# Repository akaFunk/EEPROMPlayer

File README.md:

# EEPROMPlayer
The EEPROMPlayer is an audio player that can play audio from an (E)EPROM using no microcontroller, but only simple logic ICs and an analog audio amplifier.

The EPROM used is compatible to standard 27C010 EPROMs. The clock is generated using an NE555 timer and then diveded several times using 74LS74 flip-flops. Each clock signal is fed to one of the address lines of the EPROM. The EPROM holds the raw audio data in 8 bit. The 8 data lines are passed into an R2R-network which does the digital to analog conversion. An LM386 is used to amplify the signal.

## Images

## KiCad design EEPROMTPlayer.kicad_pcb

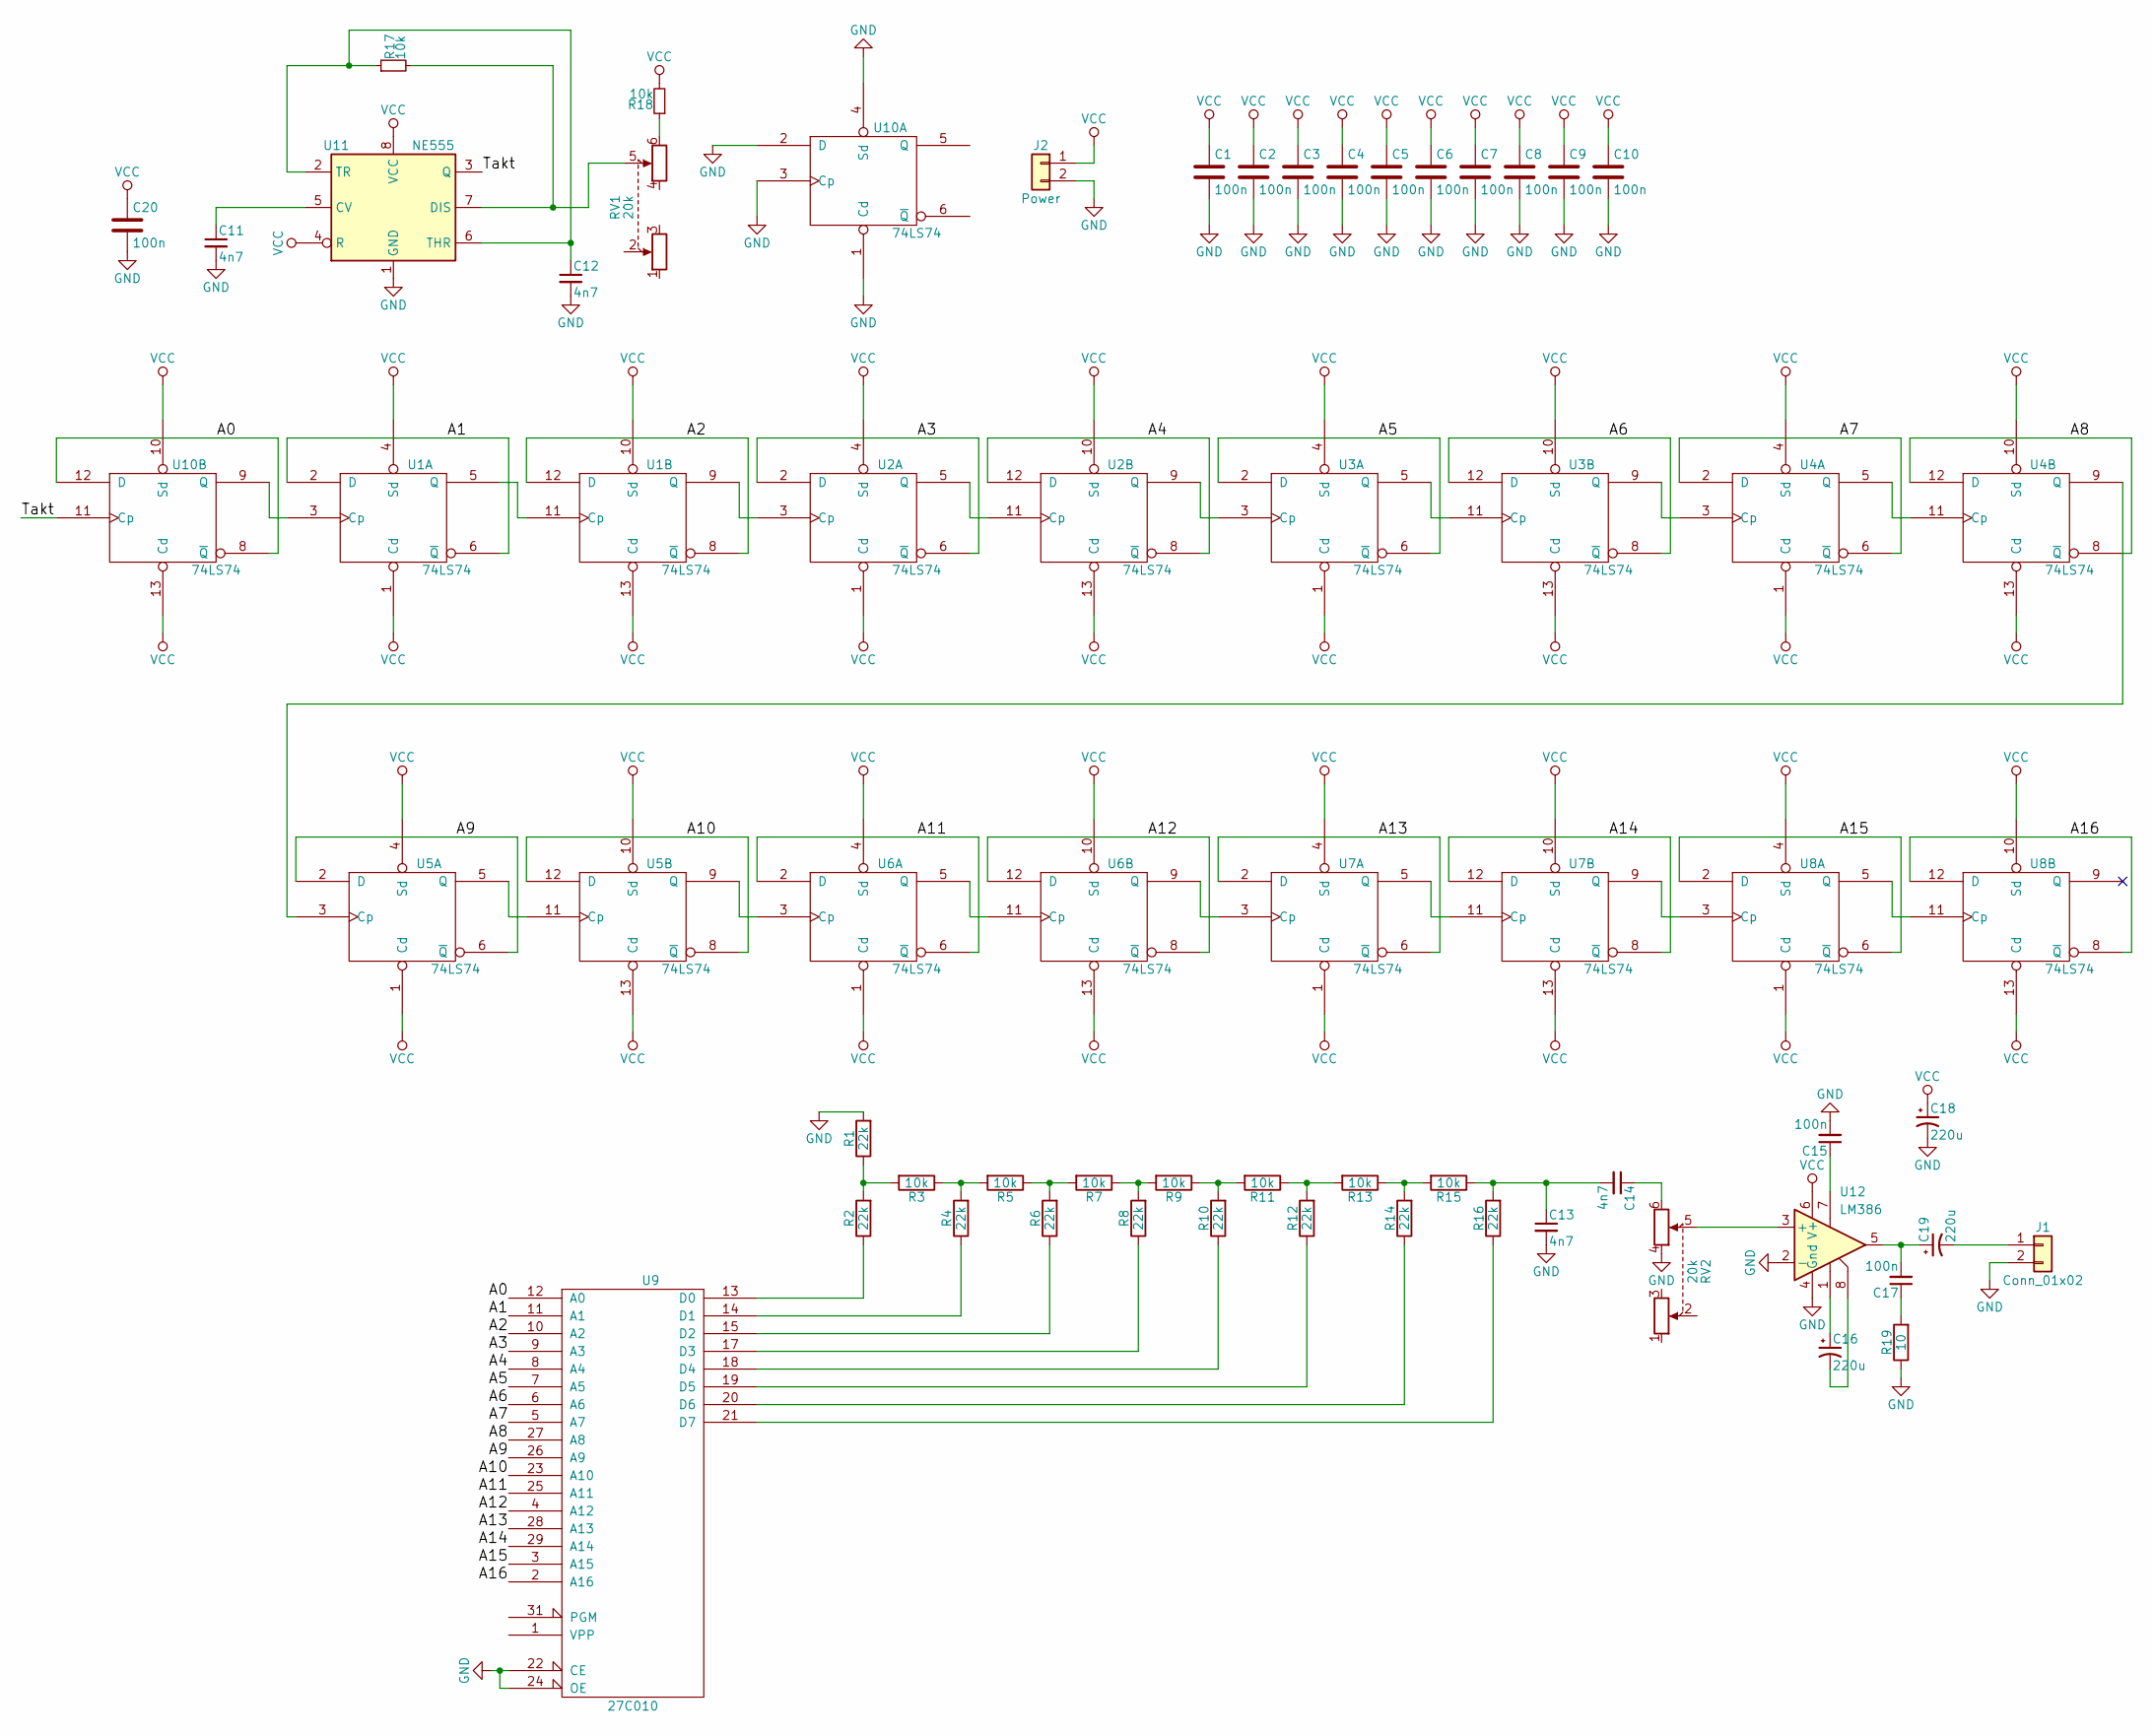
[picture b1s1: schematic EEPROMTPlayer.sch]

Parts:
C1, C2, C3, C4, C5, C6, C7, C8, C9, C10, C15, C17, C20: 100n; C_Disc_D3.0mm_W1.6mm_P2.50mm
C11, C12, C13, C14: 4n7; C_Disc_D12.5mm_W5.0mm_P10.00mm
C16, C18, C19: 220u; CP_Radial_D6.3mm_P2.50mm
J1: Conn_01x02; Pin_Header_Straight_1x02_Pitch2.54mm
J2: Power; Pin_Header_Straight_1x02_Pitch2.54mm
R1, R2, R4, R6, R8, R10, R12, R14, R16: 22k; R_Axial_DIN0204_L3.6mm_D1.6mm_P7.62mm_Horizontal
R3, R5, R7, R9, R11, R13, R15: 10k; R_Axial_DIN0204_L3.6mm_D1.6mm_P2.54mm_Vertical
R17, R18: 10k; R_Axial_DIN0204_L3.6mm_D1.6mm_P7.62mm_Horizontal
R19: 10; R_Axial_DIN0204_L3.6mm_D1.6mm_P7.62mm_Horizontal
RV1, RV2: 20k; Potentiometer_Alps_RK163_Double_Vertical
U1, U2, U3, U4, U5, U6, U7, U8, U10: 74LS74; DIP-14_W7.62mm_LongPads
U9: 27C010; DIP-32_W15.24mm_LongPads
U11: NE555; DIP-8_W7.62mm_LongPads
U12: LM386; DIP-8_W7.62mm_LongPads

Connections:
/A0: U9.12 (A0), U10.8 (~Q), U10.12 (D)
/A1: U1.2 (D), U1.6 (~Q), U9.11 (A1)
/A2: U1.8 (~Q), U1.12 (D), U9.10 (A2)
/A3: U2.2 (D), U2.6 (~Q), U9.9 (A3)
/A4: U2.8 (~Q), U2.12 (D), U9.8 (A4)
/A5: U3.2 (D), U3.6 (~Q), U9.7 (A5)
/A6: U3.8 (~Q), U3.12 (D), U9.6 (A6)
/A7: U4.2 (D), U4.6 (~Q), U9.5 (A7)
/A8: U4.8 (~Q), U4.12 (D), U9.27 (A8)
/A9: U5.2 (D), U5.6 (~Q), U9.26 (A9)
/A10: U5.8 (~Q), U5.12 (D), U9.23 (A10)
/A11: U6.2 (D), U6.6 (~Q), U9.25 (A11)
/A12: U6.8 (~Q), U6.12 (D), U9.4 (A12)
/A13: U7.2 (D), U7.6 (~Q), U9.28 (A13)
/A14: U7.8 (~Q), U7.12 (D), U9.29 (A14)
/A15: U8.2 (D), U8.6 (~Q), U9.3 (A15)
/A16: U8.8 (~Q), U8.12 (D), U9.2 (A16)
/Takt: U10.11 (Cp), U11.3 (Q)
GND: C1.2, C2.2, C3.2, C4.2, C5.2, C6.2, C7.2, C8.2, C9.2, C10.2, C11.2, C12.2, C13.2, C15.2, C18.2, C20.2, J1.2, J2.2, R1.2, R19.1, RV2.4, U1.7 (GND), U2.7 (GND), U3.7 (GND), U4.7 (GND), U5.7 (GND), U6.7 (GND), U7.7 (GND), U8.7 (GND), U9.16 (GND), U9.22 (CE), U9.24 (OE), U10.1 (Cd), U10.2 (D), U10.3 (Cp), U10.4 (Sd), U10.7 (GND), U11.1 (GND), U12.2 (-), U12.4 (Gnd)
unnamed: C11.1, U11.5 (CV)
unnamed: C12.1, R17.1, U11.2 (TR), U11.6 (THR)
unnamed: C13.1, C14.2, R15.1, R16.2
unnamed: C14.1, RV2.6
unnamed: C15.1, U12.7
unnamed: C16.1, U12.1
unnamed: C16.2, U12.8
unnamed: C17.1, R19.2
unnamed: C17.2, C19.1, U12.5
unnamed: C19.2, J1.1
unnamed: R1.1, R2.2, R3.2
unnamed: R2.1, U9.13 (D0)
unnamed: R3.1, R4.2, R5.2
unnamed: R4.1, U9.14 (D1)
unnamed: R5.1, R6.2, R7.2
unnamed: R6.1, U9.15 (D2)
unnamed: R7.1, R8.2, R9.2
unnamed: R8.1, U9.17 (D3)
unnamed: R10.1, U9.18 (D4)
unnamed: R9.1, R10.2, R11.2
unnamed: R11.1, R12.2, R13.2
unnamed: R12.1, U9.19 (D5)
unnamed: R13.1, R14.2, R15.2
unnamed: R14.1, U9.20 (D6)
unnamed: R16.1, U9.21 (D7)
unnamed: R17.2, RV1.5, U11.7 (DIS)
unnamed: R18.1, RV1.6
unnamed: RV2.5, U12.3 (+)
unnamed: U1.3 (Cp), U10.9 (Q)
unnamed: U1.9 (Q), U2.3 (Cp)
unnamed: U1.5 (Q), U1.11 (Cp)
unnamed: U2.9 (Q), U3.3 (Cp)
unnamed: U2.5 (Q), U2.11 (Cp)
unnamed: U3.9 (Q), U4.3 (Cp)
unnamed: U3.5 (Q), U3.11 (Cp)
unnamed: U4.9 (Q), U5.3 (Cp)
unnamed: U4.5 (Q), U4.11 (Cp)
unnamed: U5.9 (Q), U6.3 (Cp)
unnamed: U5.5 (Q), U5.11 (Cp)
unnamed: U6.9 (Q), U7.3 (Cp)
unnamed: U6.5 (Q), U6.11 (Cp)
unnamed: U7.9 (Q), U8.3 (Cp)
unnamed: U7.5 (Q), U7.11 (Cp)
unnamed: U8.5 (Q), U8.11 (Cp)
VCC: C1.1, C2.1, C3.1, C4.1, C5.1, C6.1, C7.1, C8.1, C9.1, C10.1, C18.1, C20.1, J2.1, R18.2, U1.1 (Cd), U1.4 (Sd), U1.10 (Sd), U1.13 (Cd), U1.14 (VCC), U2.1 (Cd), U2.4 (Sd), U2.10 (Sd), U2.13 (Cd), U2.14 (VCC), U3.1 (Cd), U3.4 (Sd), U3.10 (Sd), U3.13 (Cd), U3.14 (VCC), U4.1 (Cd), U4.4 (Sd), U4.10 (Sd), U4.13 (Cd), U4.14 (VCC), U5.1 (Cd), U5.4 (Sd), U5.10 (Sd), U5.13 (Cd), U5.14 (VCC), U6.1 (Cd), U6.4 (Sd), U6.10 (Sd), U6.13 (Cd), U6.14 (VCC), U7.1 (Cd), U7.4 (Sd), U7.10 (Sd), U7.13 (Cd), U7.14 (VCC), U8.1 (Cd), U8.4 (Sd), U8.10 (Sd), U8.13 (Cd), U8.14 (VCC), U9.32 (VCC), U10.10 (Sd), U10.13 (Cd), U10.14 (VCC), U11.4 (R), U11.8 (VCC), U12.6 (V+)

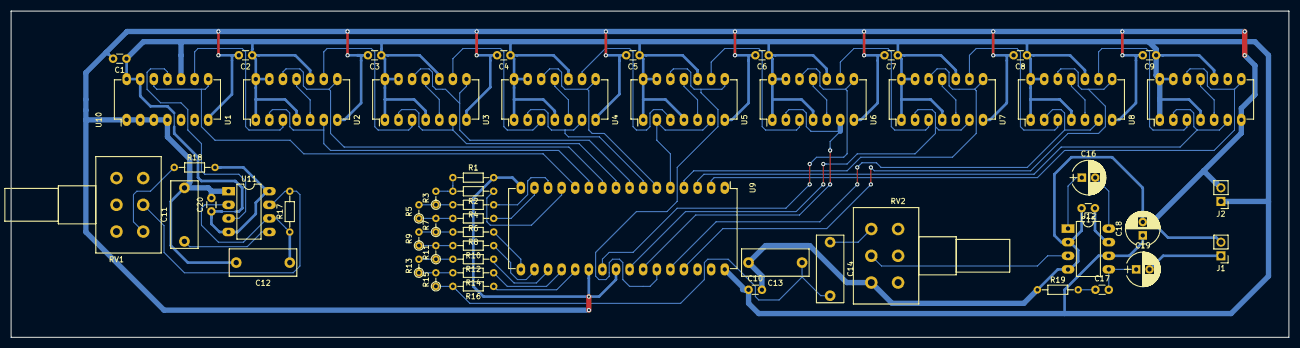
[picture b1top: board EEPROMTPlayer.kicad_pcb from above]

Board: 2 copper layers, 238.8 x 61.0 mm, 55 parts (0 on the bottom side), 64 nets.

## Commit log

2018-08-01 Updated wrong file names in the files
2018-08-01 Added images
2018-08-01 Added gerber files
2018-08-01 Removed wrong files
2018-08-01 Added readme
2018-08-16 Added license
